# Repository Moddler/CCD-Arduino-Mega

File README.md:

# CCD-Arduino-Mega

! Work in Progress - Entirely untested !

An Arduino mega shield for interfacing with Chrysler's legacy CCD databus.

This project is a shield for the Arduino Mega 2560. It is designed to hold all the parts necessary to interface with Chrysler's legacy databus CCD, utilized in Chrysler vehicles from the late 80s to late 90s.

The shield can hold a CCD chip in PDIP 14 formfactor, which enables the communication between Arduino Mega and a CCD-databus. For this scenario a quartz oscillator is needed on the PCB.

Known variants/labels of this chip are:

- Intersil CDP68HC68S1E (PDIP 14)
- Harris 4374040 (PDIP 14)
- Harris 306846 (PDIP 14)
- Signetics 4517535 (PDIP 14)

- Intersil CDP68HC68S1M (SOIC 20)
- Philips 4651148 (SOIC 20)
- Philips 04833637 (SOIC 20)
- Signetics 4632650 (SOIC 20)

Additionally, this board can hold the CCDBusTranceiver_v300 from https://github.com/laszlodaniel/CCDBusTransceiver
No oscillator is needed here, this is the preferred method.

There are three jumpers available for setting bus termination and bus bias voltage.

A pushbutton and two LEDs are also available for whatever one could use them.

There is no specific software available at this point.

This device is meant to be able to tinker with ECUs/BCMs/EATX-Controllers etc. on a testbench, without having to worry about the circuits around the CCD interfacing-chip.

It probably can also be used to sniff CCD messages in a vehicle, or trigger diagnostic commands.
It is not a full blown diagnostic device and will never be, since it is missing some other features Chrysler used in old vehicles.

The board is powered via the USB connection of the Arduino, and also enables the serial communication with a serial console or program.
The simplest way to get started is to use the serial passthrough example sketch and set the baud rate communication to the chip to 7812,5 Baud (CCD bus baud speed).

Related and highly respected work:

Juha Niinikoski
http://www.kolumbus.fi/juha.niinikoski/CCD_bus/ccd_display.htm

Boundary Condition / László Dániel
https://chryslerccdsci.wordpress.com
https://github.com/laszlodaniel/ChryslerCCDSCIScanner
https://github.com/laszlodaniel/CCDLibrary
https://github.com/laszlodaniel/CCDBusTransceiver

Geoff / moparchem.com / Ladybug / Dcal

ShelGame at turbo-mopar.com
http://www.turbo-mopar.com/forums/member.php?141-ShelGame

wowzer at turbo-mopar.com
http://www.turbo-mopar.com/forums/member.php?1068-wowzer

majekw
https://github.com/majekw/sigrok-ccd-pd

xerootg
https://github.com/xerootg

NickInTimeDesign
https://nickintimedesign.com

AR1972
https://github.com/AR1972/jeep_2.5L

MWisBest
https://github.com/MWisBest/DRBDBReader

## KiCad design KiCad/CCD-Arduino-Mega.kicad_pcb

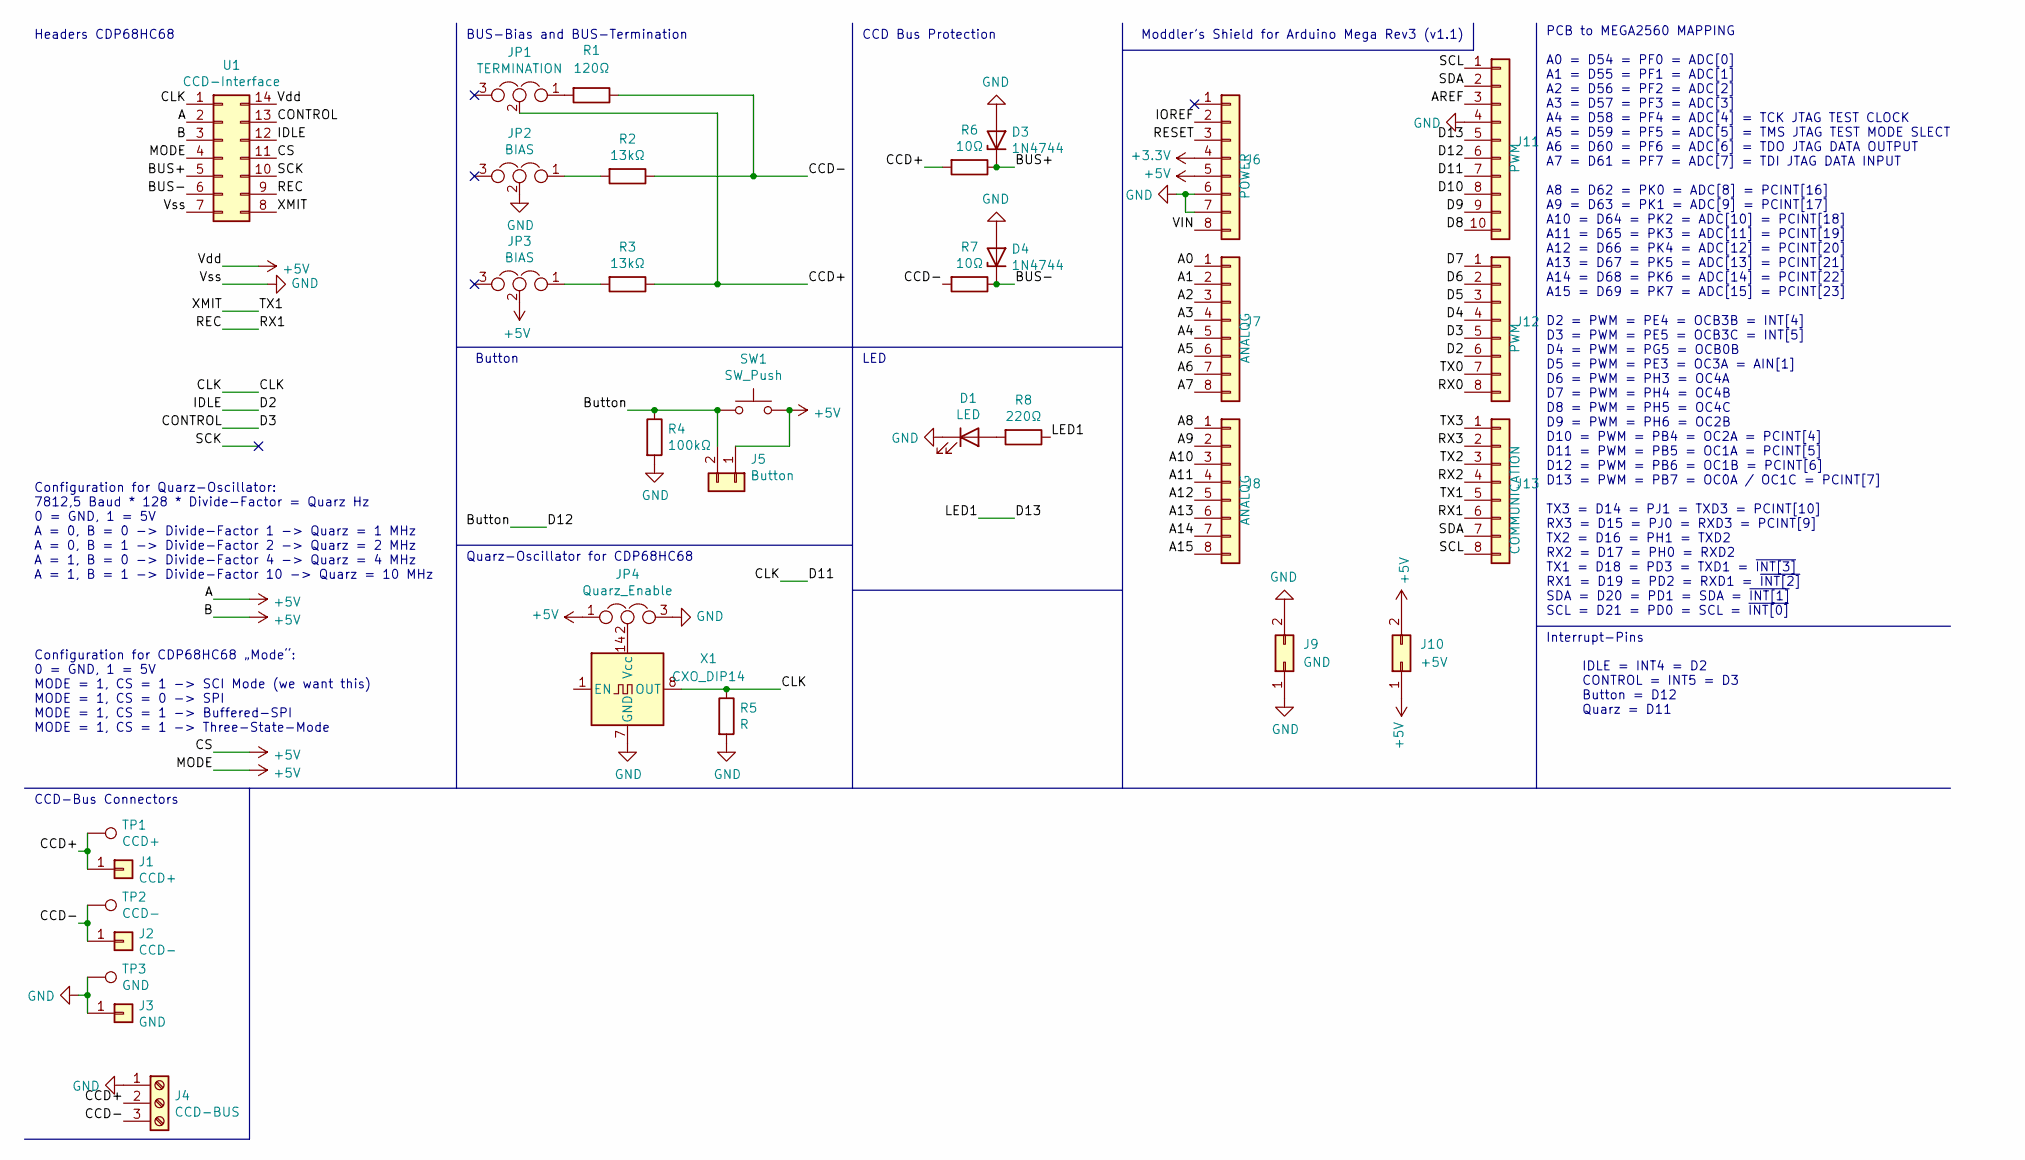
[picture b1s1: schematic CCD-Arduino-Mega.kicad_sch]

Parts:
D1: LED; LED_D5.0mm
D3, D4: 1N4744; D_DO-41_SOD81_P7.62mm_Horizontal
J1: CCD+; PinSocket_1x01_P2.54mm_Vertical
J2: CCD-; PinSocket_1x01_P2.54mm_Vertical
J3: GND; PinSocket_1x01_P2.54mm_Vertical
J4: CCD-BUS; TerminalBlock_Phoenix_MPT-0,5-3-2.54_1x03_P2.54mm_Horizontal
J5: Button; PinHeader_1x02_P2.54mm_Vertical
J6: POWER; PinHeader_1x08_P2.54mm_Vertical
J7, J8: ANALOG; PinHeader_1x08_P2.54mm_Vertical
J9: GND; PinHeader_2x01_P2.54mm_Vertical
J10: +5V; PinHeader_2x01_P2.54mm_Vertical
J11: PWM; PinHeader_1x10_P2.54mm_Vertical
J12: PWM; PinHeader_1x08_P2.54mm_Vertical
J13: COMMUNICATION; PinHeader_1x08_P2.54mm_Vertical
JP1: TERMINATION; PinHeader_1x03_P2.54mm_Vertical
JP2, JP3: BIAS; PinHeader_1x03_P2.54mm_Vertical
JP4: Quarz_Enable; PinHeader_1x03_P2.54mm_Vertical
R1: 120Ω; R_Axial_DIN0207_L6.3mm_D2.5mm_P7.62mm_Horizontal
R2, R3: 13kΩ; R_Axial_DIN0207_L6.3mm_D2.5mm_P7.62mm_Horizontal
R4: 100kΩ; R_Axial_DIN0207_L6.3mm_D2.5mm_P7.62mm_Horizontal
R5: R; R_Axial_DIN0207_L6.3mm_D2.5mm_P7.62mm_Horizontal
R6, R7: 10Ω; R_Axial_DIN0207_L6.3mm_D2.5mm_P7.62mm_Horizontal
R8: 220Ω; R_Axial_DIN0207_L6.3mm_D2.5mm_P7.62mm_Horizontal
SW1: SW_Push; SW_PUSH_6mm
TP1: CCD+; TestPoint_Pad_D3.0mm
TP2: CCD-; TestPoint_Pad_D3.0mm
TP3: GND; TestPoint_Pad_D3.0mm
U1: CCD-Interface; DIP_Socket-14_W4.3_W5.08_W7.62_W10.16_W10.9_3M_214-3339-00-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
X1: CXO_DIP14; Oscillator_DIP-14

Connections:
+3V3: J6.4
+5V: J5.1, J6.5, J10.1, J10.2, JP3.2, JP4.1, SW1.2, U1.2, U1.3, U1.4, U1.11, U1.14
/A0: J7.1
/A1: J7.2
/A2: J7.3
/A3: J7.4
/A4: J7.5
/A5: J7.6
/A6: J7.7
/A7: J7.8
/A8: J8.1
/A9: J8.2
/A10: J8.3
/A11: J8.4
/A12: J8.5
/A13: J8.6
/A14: J8.7
/A15: J8.8
/AREF: J11.3
/BUS+: D3.1 (K), R6.1, U1.5
/BUS-: D4.1 (K), R7.1, U1.6
/Button: J5.2, J11.6, R4.1, SW1.1
/CCD+: J1.1, J4.2, JP1.2, R3.1, R6.2, TP1.1
/CCD-: J2.1, J4.3, R1.1, R2.1, R7.2, TP2.1
/CLK: J11.7, R5.1, U1.1, X1.8 (OUT)
/CONTROL: J12.5, U1.13
/D2: J12.6, U1.12
/D4: J12.4
/D5: J12.3
/D6: J12.2
/D7: J12.1
/D8: J11.10
/D9: J11.9
/D10: J11.8
/D13: J11.5, R8.1
/IOREF: J6.2
/REC: J13.6, U1.9
/RESET: J6.3
/RX0: J12.8
/RX2: J13.4
/RX3: J13.2
/SCK: U1.10
/SCL: J11.1, J13.8
/SDA: J11.2, J13.7
/TX0: J12.7
/TX1: J13.5, U1.8
/TX2: J13.3
/TX3: J13.1
/VIN: J6.8
GND: D1.1 (K), D3.2 (A), D4.2 (A), J3.1, J4.1, J6.6, J6.7, J9.1, J9.2, J11.4, JP2.2, JP4.3, R4.2, R5.2, TP3.1, U1.7, X1.7 (GND)
unnamed: D1.2 (A), R8.2
unnamed: JP1.1, R1.2
unnamed: JP2.1, R2.2
unnamed: JP3.1, R3.2
unnamed: JP4.2, X1.14 (Vcc)

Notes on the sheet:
LED
Quarz-Oscillator for CDP68HC68
IDLE = INT4 = D2 CONTROL = INT5 = D3 Button = D12 Quarz = D11
Configuration for Quarz-Oscillator: 7812,5 Baud * 128 * Divide-Factor = Quarz Hz 0 = GND, 1 = 5V A = 0, B = 0 -> Divide-Factor 1 -> Quarz = 1 MHz A = 0, B = 1 -> Divide-Factor 2 -> Quarz = 2 MHz A = 1, B = 0 -> Divide-Factor 4 -> Quarz = 4 MHz A = 1, B = 1 -> Divide-Factor 10 -> Quarz = 10 MHz
Interrupt-Pins
CCD-Bus Connectors
Button
BUS-Bias and BUS-Termination
PCB to MEGA2560 MAPPING A0 = D54 = PF0 = ADC[0] A1 = D55 = PF1 = ADC[1] A2 = D56 = PF2 = ADC[2] A3 = D57 = PF3 = ADC[3] A4 = D58 = PF4 = ADC[4] = TCK JTAG TEST CLOCK A5 = D59 = PF5 = ADC[5] = TMS JTAG TEST MODE SLECT A6 = D60 = PF6 = ADC[6] = TDO JTAG DATA OUTPUT A7 = D61 = PF7 = ADC[7] = TDI JTAG 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
CCD Bus Protection
Configuration for CDP68HC68 „Mode“: 0 = GND, 1 = 5V MODE = 1, CS = 1 -> SCI Mode (we want this) MODE = 1, CS = 0 -> SPI MODE = 1, CS = 1 -> Buffered-SPI MODE = 1, CS = 1 -> Three-State-Mode
Headers CDP68HC68
Moddler’s Shield for Arduino Mega Rev3 (v1.1)

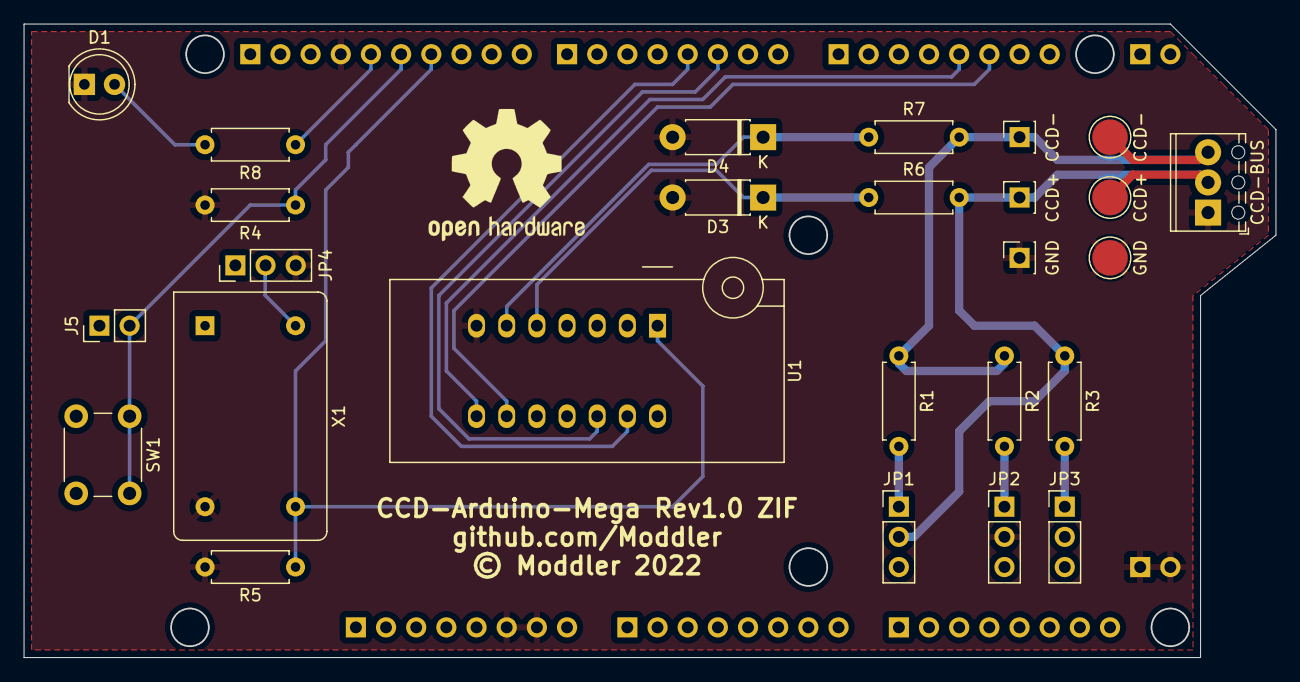
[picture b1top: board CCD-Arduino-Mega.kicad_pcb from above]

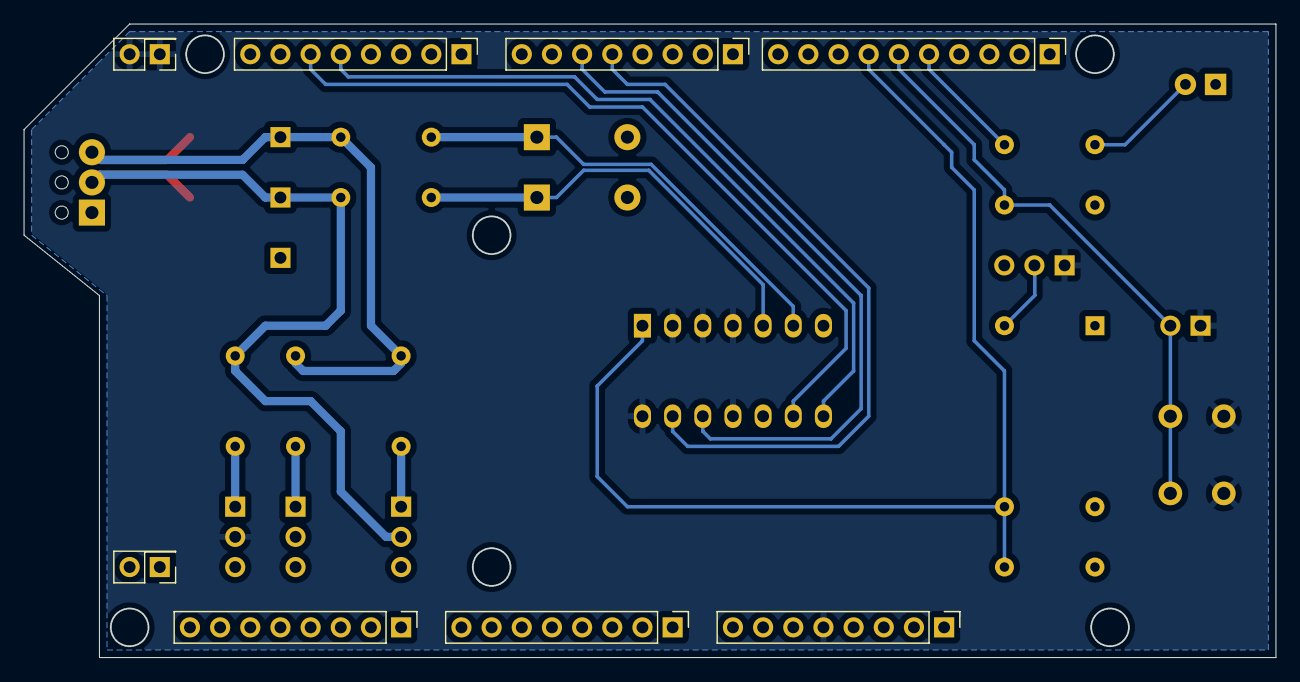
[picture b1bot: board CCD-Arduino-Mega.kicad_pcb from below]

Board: 2 copper layers, 105.3 x 53.2 mm, 34 parts (8 on the bottom side), 20 nets.

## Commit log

2022-03-07 reboot and update to KiCAD v7
2022-03-18 implement ZIF-Socket
2022-03-18 adjust trackwidth
2022-03-19 reboot and update to KiCAD v6
2022-03-19 remove LED, connect CLK; Revision 1.0
2022-03-19 fab settings
2022-04-24 Add "ZIF" to PCB
2022-05-23 Update CCD-Arduino-Mega.kicad_sch
    correct CCD-bus termination resistor value
2022-07-11 correction R value

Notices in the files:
KiCad/CCD-Arduino-Mega.kicad_pcb:
© Moddler 2022
